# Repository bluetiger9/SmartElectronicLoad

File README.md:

# SmartElectronicLoad
A smart electronic load

## Component Selection

1. Current Sense Amplifier OpAmp:
   - amplifies the voltage drop from the current sense resistors
   - low input offset (<=1mV, lower is better) - offset is amplified with the same amount as the sense current
   - high gain bandwidth product (>=5-10MHz, higher is better) - can limit the overall bandwidth of the load - for ex. 5MHz GBP with 10x amplification results in a 0.5Mhz effective bandwidth
   - input and output must go down to negative rail (0V)
   - input and output may not go up to the positive rail (3V3/12V) - in this case current range is reduced according to the upper limits
   - supply: 0-3V3 (or 0-12V)

2. Load Set OpAmp:
   - controls the gate of the load MOSFETs
   - input and output must go down to the negative rail (0V)
   - gain bandwidth product (>=1MHz) - can limit the overall bandwidth of the load
   - supply: 0-12V

3. Voltage Sense Buffer / Current Sense Buffer OpAmps
   - acts as a buffer for the voltage sense signals
   - input and output must go down to the negative rail (0V)
   - input and output may not go up to the positive rail (3V3/12V) - in this case voltage / current sense ranges are reduces accordingly
   - supply: 0-3V3 (or 0-12V)

4. DAC Buffer OpAmp
   - acts as a buffer for the DAC output
   - input and output must go down to the negative rail (0V)
   - input and output may not go up to the positive rail (3V3/12V) - in this case current range is reduced according to the upper limits
   - supply: 0-3V3 (or 0-12V)

5. MOSFET-s
   - acts as the active dissipates power element
   - N-channel MOSFET in TO-247 or TO-220 package
   - thermal resistance (lower is better) drive heat dissipation capacity
   - switching speed can affect the overall load bandwidth
   - drain source voltage limits the maximum voltage of the load
   - ON state resistance limits the maximum current at low voltages
   - can be in isolated or non-isolated package - non-isolated need additional parts to avoid exposing the load voltage on the heat sink

6. Current Sense Resistor
   - used to measure the current dissipated by the load
   - should be in the range of 5mV-100mΩ - resistor value in combination with multiplication factor gives the current range of the load - ex. 10mΩ + 10x (@3.3V) results in a 0-33A range (per channel)
   - SMD-2512 package
   - two resistors can be placed in parallel to the lower heat dissipation (which causes drift)

7. ESP32 SoC
   - the "brain" of the load
   - ESP32-S3-WROOM-1 modules (or ESP32-S2-SOLO-2, not recommended as it only has one core, and the built in DAC is no longer used)
   - 4MB+ flash, optional PSRAM (Quad SPI only - Octal SPI variants disable some GPIO pins)

## Bandwidth / Stability Tunning:
1. C1/R9 (and C2/R10) sets the overall bandwidth of the load
   - ex. 330Ω with 4.7nF results in a bandwidth of a ~100kHz
   - bandwidth can be increased by changing C1/C2 (or R9/R10) - ex 1nF achieves a bandwidth ~480kHz
     (*note: the current sense and load set OpAmps must keep up)

2. R65 (and R69) sets the MOSFETs gate current
   - default value is 10Ω
   - in case of oscillations, changing this resistor to a higher (ex. 47Ω) or lower (?) value (ex. 1Ω) may help stabilizing the load

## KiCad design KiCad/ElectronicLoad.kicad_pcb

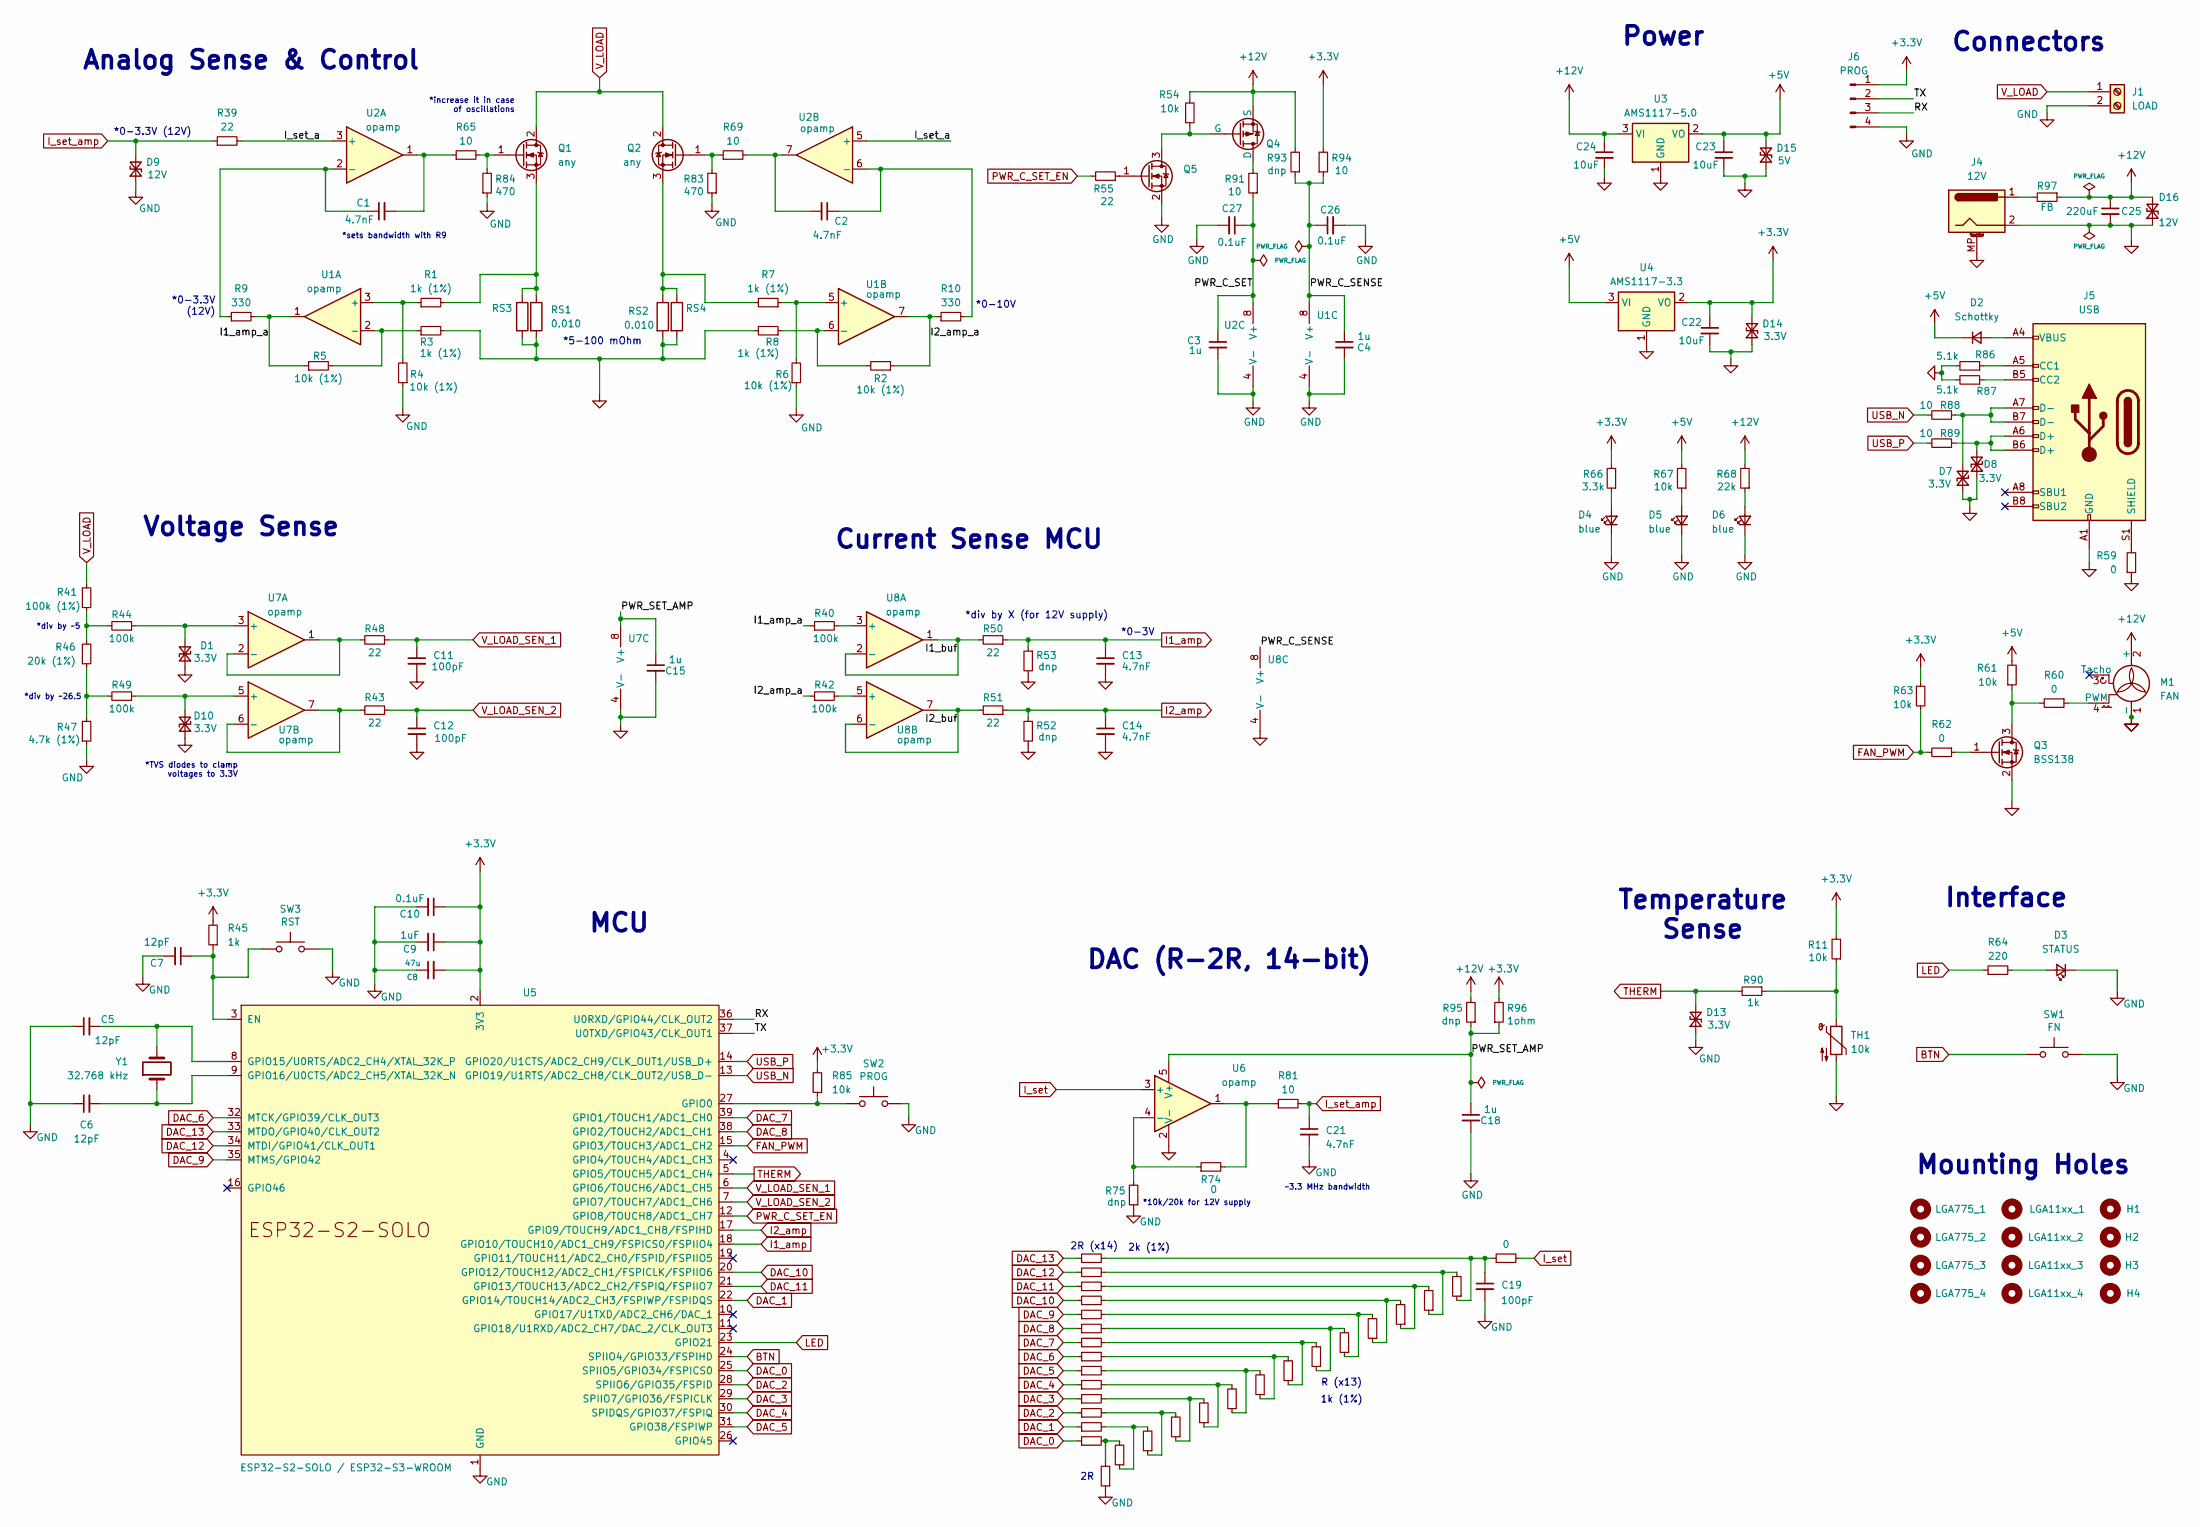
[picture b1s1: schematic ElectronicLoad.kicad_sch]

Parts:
C1, C2, C13, C14, C21: 4.7nF; C_0603_1608Metric
C3, C4, C15, C18: 1u; C_0603_1608Metric
C5, C6: 12pF; C_0603_1608Metric
C7: 12pF; C_0805_2012Metric
C8: 47u; C_0805_2012Metric
C9: 1uF; C_0805_2012Metric
C10, C26, C27: 0.1uF; C_0805_2012Metric
C11, C12, C19: 100pF; C_0603_1608Metric
C22, C23, C24: 10uF; C_0805_2012Metric
C25: 220uF; C_Elec_6.3x7.7
D1, D7, D8, D10, D13: 3.3V; D_SOD-323_HandSoldering
D2: Schottky; D_SOD-123
D3: STATUS; LED_0805_2012Metric
D4, D5, D6: blue; LED_0805_2012Metric
D9: 12V; D_SOD-323_HandSoldering
D14: 3.3V; D_SOD-123
D15: 5V; D_SOD-123
D16: 12V; D_SOD-123
H1, H2, H3, H4: MountingHole; MountingHole_4.3mm_M4
J1: LOAD; Terminal-Block-7-screw
J4: 12V; BarrelJack_Horizontal
J5: USB; USB_C_Receptacle_G-Switch_GT-USB-7010ASV
J6: PROG; PinHeader_1x04_P2.54mm_Vertical
LGA11xx_1, LGA11xx_2, LGA11xx_3, LGA11xx_4, LGA775_1, LGA775_2, LGA775_3, LGA775_4: MountingHole; MountingHole_4mm
M1: FAN; FanPinHeader_1x04_P2.54mm_Vertical
Q1, Q2: any; TO-247-220
Q3, Q5: BSS138; SOT-23
Q4: PMOS; SOT-23
R1, R3, R7, R8, R25, R26, R27, R28, R29, R30, R31, R32, R33, R34, R35, R36, R37: 1k (1%); R_0603_1608Metric
R2, R4, R5, R6: 10k (1%); R_0603_1608Metric
R9, R10: 330; R_0603_1608Metric
R11, R54, R61, R63, R67, R85: 10k; R_0805_2012Metric
R12, R13, R14, R15, R16, R17, R18, R19, R20, R21, R22, R23, R24, R38, R201: 2k (1%); R_0603_1608Metric
R39, R43, R48, R50, R51: 22; R_0603_1608Metric
R40, R42, R44, R49: 100k; R_0603_1608Metric
R41: 100k (1%); R_0603_1608Metric
R45, R90: 1k; R_0805_2012Metric
R46: 20k (1%); R_0603_1608Metric
R47: 4.7k (1%); R_0603_1608Metric
R52, R53, R75: dnp; R_0603_1608Metric
R55: 22; R_0805_2012Metric
R59, R60, R62: 0; R_0805_2012Metric
R64: 220; R_0805_2012Metric
R65, R69, R81, R88, R89: 10; R_0603_1608Metric
R66: 3.3k; R_0805_2012Metric
R68: 22k; R_0805_2012Metric
R70, R74: 0; R_0603_1608Metric
R83, R84: 470; R_0603_1608Metric
R86, R87: 5.1k; R_0603_1608Metric
R91, R94: 10; R_0805_2012Metric
R93, R95: dnp; R_0805_2012Metric
R96: 1ohm; R_0805_2012Metric
R97: FB; R_0805_2012Metric
RS1, RS2: 0.010; R_2512_6332Metric
RS3, RS4: 0.001; R_2512_6332Metric
SW1: FN; SW_SPST_TL3342
SW2: PROG; SW_SPST_TL3342
SW3: RST; SW_SPST_TL3342
TH1: 10k; PinHeader_1x02_P2.00mm_Vertical
U1, U2, U7, U8: opamp; SOIC-8_3.9x4.9mm_P1.27mm
U3: AMS1117-5.0; SOT-223-3_TabPin2
U4: AMS1117-3.3; SOT-223-3_TabPin2
U5: ESP32-S2-SOLO / ESP32-S3-WROOM; ESP32-S2-SOLO
U6: opamp; SOT-23-5
Y1: 32.768 kHz; Crystal_SMD_3215-2Pin_3.2x1.5mm

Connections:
+3.3V: C8.2, C9.1, C10.1, C22.1, D14.2 (A2), J6.1, R11.2, R45.2, R63.1, R66.2, R85.2, R94.2, R96.2, U4.2 (VO), U5.2 (3V3)
+5V: C23.1, D2.1 (K), D15.2 (A2), R61.2, R67.2, U3.2 (VO), U4.3 (VI)
+12V: C24.1, C25.1, D16.2 (A2), M1.2 (+), Q4.3 (S), R54.2, R68.2, R93.2, R95.2, R97.1, U3.3 (VI)
/I1_amp_a: R5.1, R9.2, R40.1, U1.1
/I1_buf: R50.2, U8.1, U8.2 (-)
/I2_amp_a: R2.1, R10.1, R42.1, U1.7
/I2_buf: R51.2, U8.6 (-), U8.7
/I_set_a: R39.2, U2.3 (+), U2.5 (+)
/PWR_C_SENSE: C4.1, C26.1, R93.1, R94.1, U1.8 (V+), U8.8 (V+)
/PWR_C_SET: C3.1, C27.1, R91.1, U2.8 (V+)
/PWR_SET_AMP: C15.1, C18.1, R95.1, R96.1, U6.5 (V+), U7.8 (V+)
/RX: J6.3, U5.36 (U0RXD/GPIO44/CLK_OUT2)
/TX: J6.2, U5.37 (U0TXD/GPIO43/CLK_OUT1)
BTN: SW1.1, U5.24 (SPIIO4/GPIO33/FSPIHD)
DAC_0: R24.1, U5.25 (SPIIO5/GPIO34/FSPICS0)
DAC_1: R23.1, U5.22 (GPIO14/TOUCH14/ADC2_CH3/FSPIWP/FSPIDQS)
DAC_2: R22.1, U5.28 (SPIIO6/GPIO35/FSPID)
DAC_3: R21.1, U5.29 (SPIIO7/GPIO36/FSPICLK)
DAC_4: R20.1, U5.30 (SPIDQS/GPIO37/FSPIQ)
DAC_5: R19.1, U5.31 (GPIO38/FSPIWP)
DAC_6: R18.1, U5.32 (MTCK/GPIO39/CLK_OUT3)
DAC_7: R17.1, U5.39 (GPIO1/TOUCH1/ADC1_CH0)
DAC_8: R16.1, U5.38 (GPIO2/TOUCH2/ADC1_CH1)
DAC_9: R15.1, U5.35 (MTMS/GPIO42)
DAC_10: R14.1, U5.20 (GPIO12/TOUCH12/ADC2_CH1/FSPICLK/FSPIIO6)
DAC_11: R13.1, U5.21 (GPIO13/TOUCH13/ADC2_CH2/FSPIQ/FSPIIO7)
DAC_12: R12.1, U5.34 (MTDI/GPIO41/CLK_OUT1)
DAC_13: R201.1, U5.33 (MTDO/GPIO40/CLK_OUT2)
FAN_PWM: R62.2, R63.2, U5.15 (GPIO3/TOUCH3/ADC1_CH2)
GND: C3.2, C4.2, C5.1, C6.1, C7.2, C8.1, C9.2, C10.2, C11.2, C12.2, C13.2, C14.2, C15.2, C18.2, C19.2, C21.2, C22.2, C23.2, C24.2, C25.2, C26.2, C27.2, D1.1 (A1), D3.1 (K), D4.1 (K), D5.1 (K), D6.1 (K), D7.1 (A1), D8.1 (A1), D9.1 (A1), D10.1 (A1), D13.1 (A1), D14.1 (A1), D15.1 (A1), D16.1 (A1), J1.2, J4.2, J4.MP (MountPin), J5.A1 (GND), J5.A12 (GND), J5.B1 (GND), J5.B12 (GND), J6.4, M1.1 (-), Q3.2 (S), Q5.2 (S), R3.2, R4.1, R6.1, R8.2, R38.1, R47.1, R52.2, R53.2, R59.1, R75.1, R83.1, R84.1, R86.2, R87.2, RS1.2, RS2.2, RS3.2, RS4.2, SW1.2, SW2.2, SW3.2, TH1.2, U1.4 (V-), U2.4 (V-), U3.1 (GND), U4.1 (GND), U5.1 (GND), U5.40 (GND), U5.41 (GND), U6.2 (V-), U7.4 (V-), U8.4 (V-)
I1_amp: C13.1, R50.1, R53.1, U5.18 (GPIO10/TOUCH10/ADC1_CH9/FSPICS0/FSPIIO4)
I2_amp: C14.1, R51.1, R52.1, U5.17 (GPIO9/TOUCH9/ADC1_CH8/FSPIHD)
I_set: R70.2, U6.3 (+)
I_set_amp: C21.1, D9.2 (A2), R39.1, R81.2
LED: R64.1, U5.23 (GPIO21)
unnamed: C1.2, R65.1, U2.1
unnamed: C2.2, R69.2, U2.7
unnamed: C19.1, R37.1, R70.1, R201.2
unnamed: D1.2 (A2), R44.1, U7.3 (+)
unnamed: D2.2 (A), J5.A4 (VBUS), J5.A9 (VBUS), J5.B4 (VBUS), J5.B9 (VBUS)
unnamed: D3.2 (A), R64.2
unnamed: D4.2 (A), R66.1
unnamed: D5.2 (A), R67.1
unnamed: D6.2 (A), R68.1
unnamed: D7.2 (A2), J5.A7 (D-), J5.B7 (D-), R88.1
unnamed: D8.2 (A2), J5.A6 (D+), J5.B6 (D+), R89.1
unnamed: D10.2 (A2), R49.1, U7.5 (+)
unnamed: J4.1, R97.2
unnamed: J5.A5 (CC1), R86.1
unnamed: J5.B5 (CC2), R87.1
unnamed: J5.S1 (SHIELD), R59.2
unnamed: M1.4 (PWM), R60.1
unnamed: Q1.1 (G), R65.2, R84.2
unnamed: Q1.3 (S), R1.2, RS1.1, RS3.1
unnamed: Q2.1 (G), R69.1, R83.2
unnamed: Q2.3 (S), R7.2, RS2.1, RS4.1
unnamed: Q3.3 (D), R60.2, R61.1
unnamed: Q3.1 (G), R62.1
unnamed: Q4.1 (D), R91.2
unnamed: Q4.2 (G), Q5.3 (D), R54.1
unnamed: Q5.1 (G), R55.1
unnamed: R11.1, R90.1, TH1.1
unnamed: R12.2, R36.1, R37.2
unnamed: R13.2, R35.1, R36.2
unnamed: R14.2, R34.1, R35.2
unnamed: R15.2, R33.1, R34.2
unnamed: R16.2, R32.1, R33.2
unnamed: R17.2, R31.1, R32.2
unnamed: R18.2, R30.1, R31.2
unnamed: R19.2, R29.1, R30.2
unnamed: R20.2, R28.1, R29.2
unnamed: R21.2, R27.1, R28.2
unnamed: R22.2, R26.1, R27.2
unnamed: R23.2, R25.1, R26.2
unnamed: R24.2, R25.2, R38.2
unnamed: R41.1, R44.2, R46.2
unnamed: R46.1, R47.2, R49.2
unnamed: R74.2, R81.1, U6.1
unnamed: R1.1, R4.2, U1.3 (+)
unnamed: R3.1, R5.2, U1.2 (-)
unnamed: R6.2, R7.1, U1.5 (+)
unnamed: R2.2, R8.1, U1.6 (-)
unnamed: C1.1, R9.1, U2.2 (-)
unnamed: C2.1, R10.2, U2.6 (-)
unnamed: C7.1, R45.1, SW3.1, U5.3 (EN)
unnamed: R85.1, SW2.1, U5.27 (GPIO0)
unnamed: C5.2, U5.8 (GPIO15/U0RTS/ADC2_CH4/XTAL_32K_P), Y1.2
unnamed: C6.2, U5.9 (GPIO16/U0CTS/ADC2_CH5/XTAL_32K_N), Y1.1
unnamed: R74.1, R75.2, U6.4 (-)
unnamed: R48.2, U7.1, U7.2 (-)
unnamed: R43.2, U7.6 (-), U7.7
unnamed: R40.2, U8.3 (+)
unnamed: R42.2, U8.5 (+)
PWR_C_SET_EN: R55.2, U5.12 (GPIO8/TOUCH8/ADC1_CH7)
THERM: D13.2 (A2), R90.2, U5.5 (GPIO5/TOUCH5/ADC1_CH4)
USB_N: R88.2, U5.13 (GPIO19/U1RTS/ADC2_CH8/CLK_OUT2/USB_D-)
USB_P: R89.2, U5.14 (GPIO20/U1CTS/ADC2_CH9/CLK_OUT1/USB_D+)
V_LOAD: J1.1, Q1.2 (D), Q2.2 (D), R41.2
V_LOAD_SEN_1: C11.1, R48.1, U5.6 (GPIO6/TOUCH6/ADC1_CH5)
V_LOAD_SEN_2: C12.1, R43.1, U5.7 (GPIO7/TOUCH7/ADC1_CH6)

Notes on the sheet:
Temperature Sense
Analog Sense & Control
Mounting Holes
*0-10V
Connectors
Interface
*5-100 mOhm
*sets bandwidth with R9
*0-3.3V (12V)
R (x13)
~3.3 MHz bandwidth
*0-3V
2k (1%)
*TVS diodes to clamp voltages to 3.3V
*div by ~26.5
*div by X (for 12V supply)
Power
*increase it in case of oscillations
1k (1%)
*10k/20k for 12V supply
Current Sense MCU
*0-3.3V (12V)
*div by ~5
2R (x14)
DAC (R-2R, 14-bit)
MCU
Voltage Sense

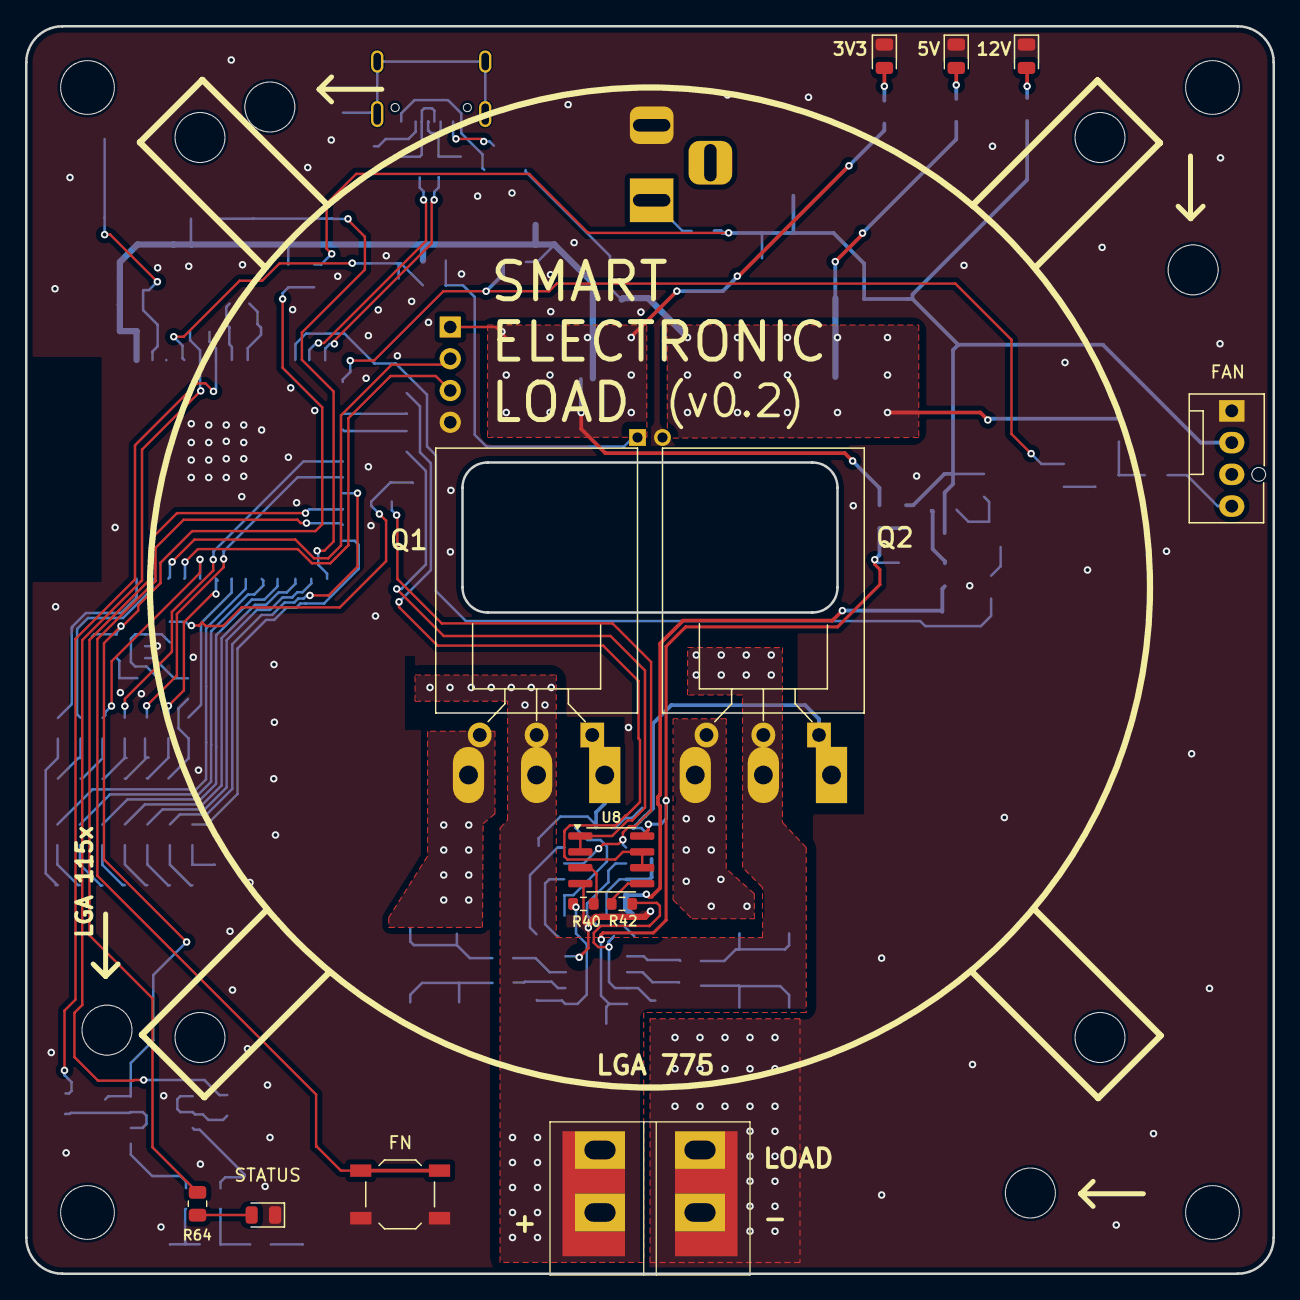
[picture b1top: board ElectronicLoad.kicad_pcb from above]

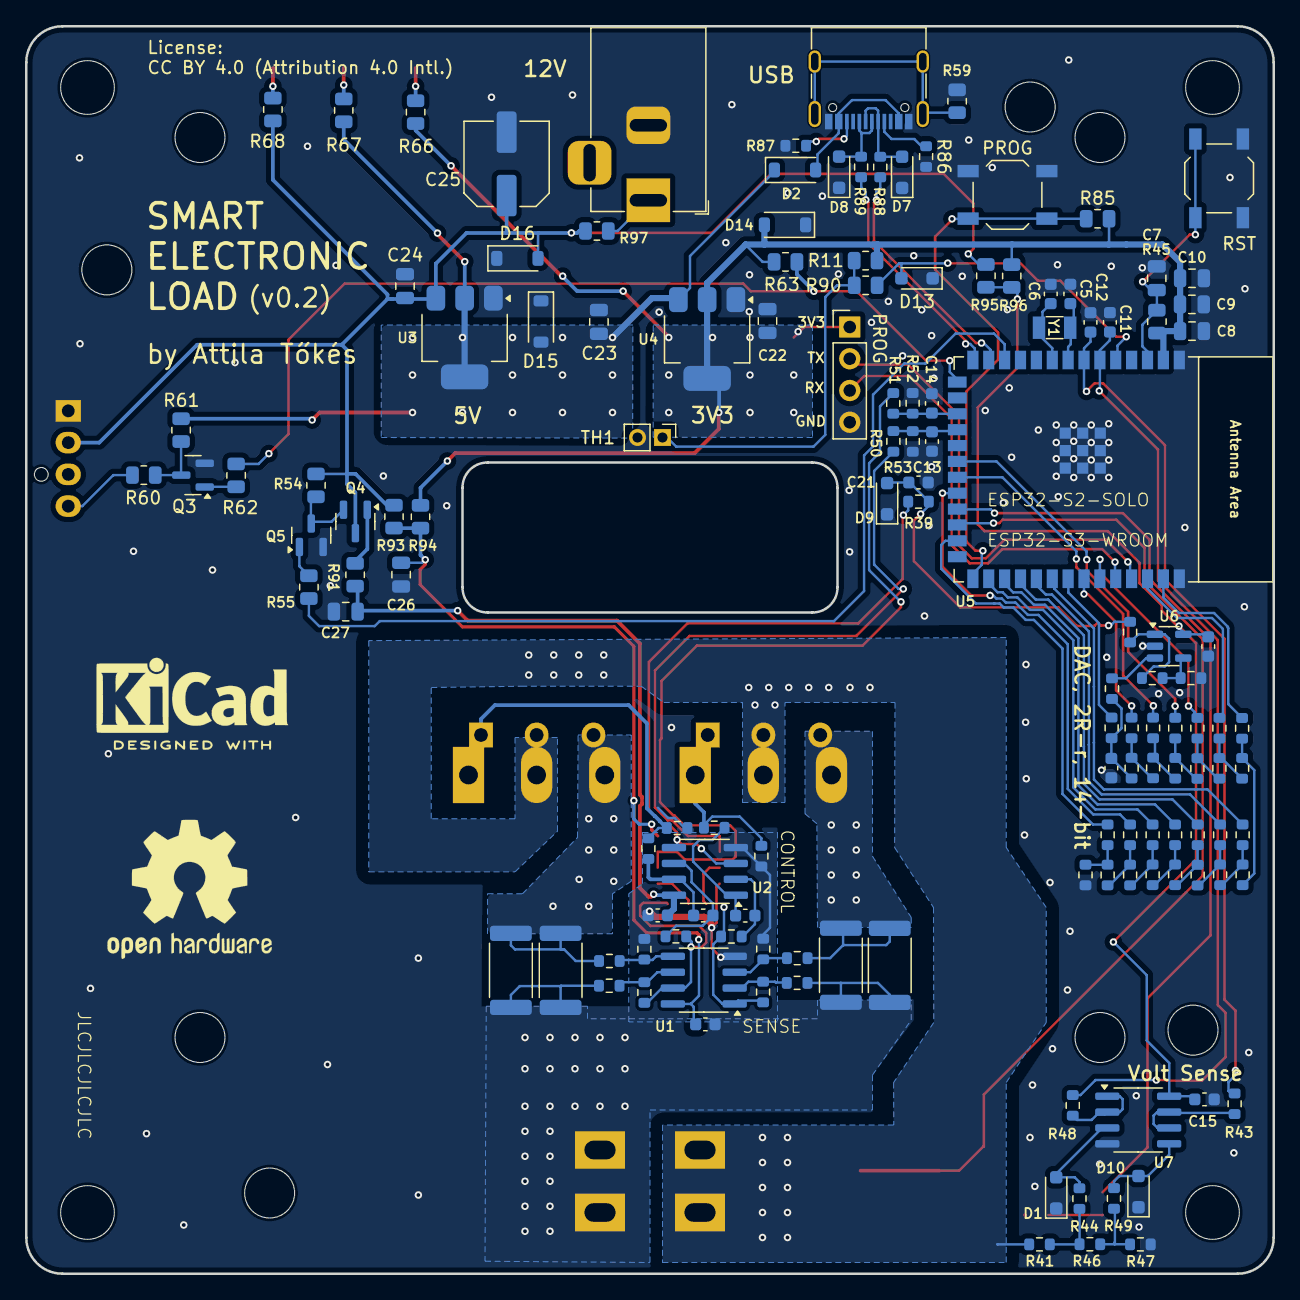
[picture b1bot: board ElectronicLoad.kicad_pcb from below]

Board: 2 copper layers, 99.8 x 99.8 mm, 162 parts (137 on the bottom side), 100 nets.

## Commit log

2024-12-30 v0.1
2025-01-07 basic firmware
2025-01-19 ESP32-S2 support + improved firmware
2025-02-02 Firmware update
2025-04-06 Firmware update (USB)
2025-11-30 rev0.2: remove DAC offset compensation and test connectors
2025-11-30 rev0.2: use only one Current Set line
2025-12-01 rev0.2: separate DAC10/11 lines from RX/TX
2025-12-01 rev0.2: remove MOSFET caps
2025-12-01 rev0.2: redesign the Voltage & (MCU) Current Sense circuits
2025-12-01 rev0.2: add duplicate current sense resistor footprint
2025-12-01 rev0.2: add disable MOSFET-s signal
2025-12-02 rev0.2: adjust component values
2025-12-29 rev 0.2 adjustments
2025-12-29 enable/disable load (+api)
2025-12-29 store state (+api)
2025-12-29 constant power and constance resistance modes (+api)
2025-12-30 process ADC reading only when they are available
2025-12-30 over temperature/current/voltage/power protection (+api)
2025-12-30 auto enable/disable on power connect/disconnect (+api)
2025-12-31 rev 0.2 schematics + pcb adjustments
2025-12-31 basic calibration support
2026-01-01 initial pulse support (+api)

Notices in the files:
KiCad/ElectronicLoad.kicad_pcb:
License:
CC BY 4.0 (Attribution 4.0 Intl.)
